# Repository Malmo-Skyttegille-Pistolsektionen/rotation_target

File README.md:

# Rotation Target

Software for running timed shooting programs on a rotating target system, built
by and for Malmö Skyttegille Pistolsektionen.

An ESP32-S3 board turns the targets face-on and edge-on to a shooting program
and plays the spoken range commands over an amplifier. A React web app — served
by the board itself over WiFi — starts and stops programs, follows the run live
over Server-Sent Events, and manages the stored programs and audio.

## ⚠️ SAFETY WARNING — READ BEFORE INSTALLING OR OPERATING

**This device moves steel on a live firing range, and it moves it on a timer.**
A target turns because a program said it was time, not because it can see who
is in front of it. It has no idea anyone is downrange.

- **The range's own safety rules and range commands govern the line. This
  software governs nothing.** A program running is not a range that is hot; a
  program stopped is not a range that is safe.
- **NEVER go downrange because the web app says the run has finished.** Confirm
  a cease-fire the way your range already requires — verbally, with firearms
  cleared and benched.
- **NEVER leave the device powered while people are forward of the firing
  line** unless your club has decided that is safe and knows what the targets
  do at power-up.
- **A target turning can injure somebody standing next to it.** Keep clear of
  the mechanism whenever the device is powered.

The targets rest **shown** at boot, deliberately: a target that turns of its own
accord when a board is powered is the failure this project is most concerned
with. That resting state can be changed to suit a target system wired the other
way round, but only over a USB cable, never from the web app — see
[Settings](https://malmo-skyttegille-pistolsektionen.github.io/rotation_target/settings/).

**Do not rely on this software to protect anyone.** It is a convenience for
running programs, not a safety device, and it has no interlock, no sensor, and
no way to know where people are.

**LIABILITY DISCLAIMER:** This project is provided as-is with absolutely no
warranty of any kind. The author(s) accept no responsibility or liability for
any injury, damage, or loss resulting from building, installing, modifying, or
operating this system. You build and use it entirely at your own risk.

---

## Documentation

Everything an operator needs is on the documentation site:

- **[Operator documentation](https://malmo-skyttegille-pistolsektionen.github.io/rotation_target/)**
  — wiring, connecting, running a program, settings, and what the status LED is
  telling you. This is the one to send a club member.
- **[Program editor](https://malmo-skyttegille-pistolsektionen.github.io/rotation_target/editor/)**
  — write and edit programs in a browser with **no device attached**, then
  download the file or open a pull request against this repository. Also useful
  for reading a shipped program without a board in front of you.
- **[Hardware and wiring](https://malmo-skyttegille-pistolsektionen.github.io/rotation_target/hardware/)**
  — what a target system has to do to work, the DB9 pinout, and the transistor
  that does the switching.

## Installing

Releases ship a pre-built firmware image; you do not need a toolchain to put it
on a board. See
[Connecting](https://malmo-skyttegille-pistolsektionen.github.io/rotation_target/connecting/)
for getting the device onto your network afterwards, and
[Settings](https://malmo-skyttegille-pistolsektionen.github.io/rotation_target/settings/)
for adapting a stock image to your own board — the target pin, its polarity,
the audio and LED pins and the device's name are all configurable on the
device, without rebuilding it.

## Target systems

- **[Eigenbrod TP2](https://eigenbrod-schiessanlagen.de/en/products?tx_produkt_produkte%5Baction%5D=show&tx_produkt_produkte%5BL%5D=2&tx_produkt_produkte%5Bprodukt%5D=319&cHash=942340d5971be0a0ac3d26ff3c257c0b)**
  — what this was built against and what it runs on.

Nothing in the firmware is specific to that system. The board speaks no
proprietary protocol to the targets: it closes and opens **one circuit**, and
the target system's own electronics do the rest. Any system driven the same way
should work.

## Layout

| Directory | Holds |
|---|---|
| [`contracts/`](contracts/README.md) | The canonical API contract: OpenAPI for REST v2, AsyncAPI for SSE v2, the program schema |
| [`firmware/`](firmware/README.md) | The ESP-IDF firmware: target IO, audio, storage, REST + SSE server |
| [`webapp/`](webapp/README.md) | The React front end, embedded in the firmware's application image |
| [`resources/`](resources/README.md) | Shipped programs and audio clips flashed onto the device |
| [`docs/`](docs/) | The [decision log](docs/DECISIONS.md), [how releases are cut](docs/RELEASING.md), and the source of the documentation site |

## Contributing

Building, flashing, running it without a device, and the coding standards are
in [`CONTRIBUTING.md`](CONTRIBUTING.md).

## License

MIT — see the `LICENSE` file in each component directory.

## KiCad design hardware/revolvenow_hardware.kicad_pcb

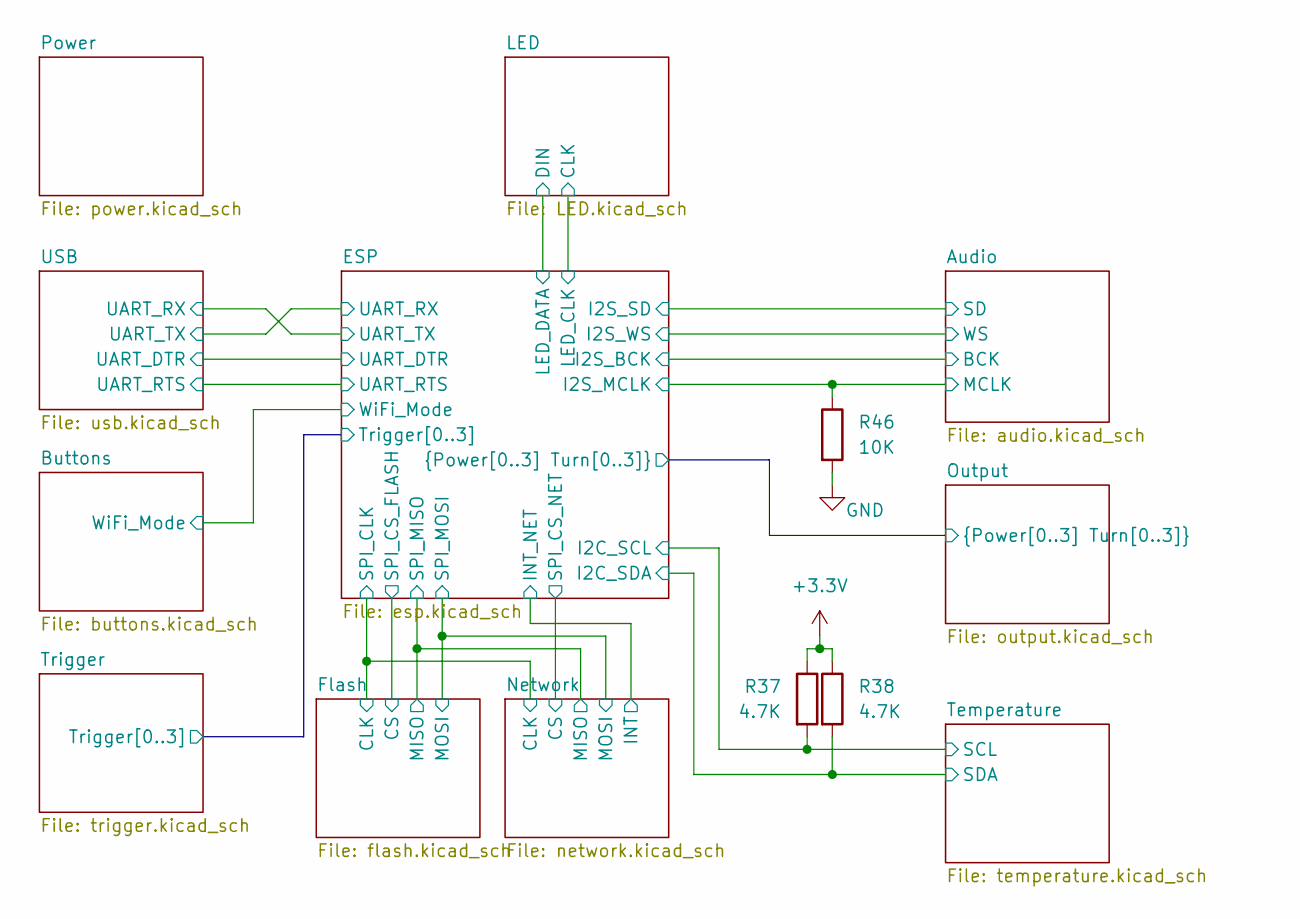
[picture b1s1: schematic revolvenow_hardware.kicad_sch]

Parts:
R37, R38: 4.7K; R_0603_1608Metric_Pad0.98x0.95mm_HandSolder
R46: 10K; R_0603_1608Metric_Pad0.98x0.95mm_HandSolder

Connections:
+3.3V: R37.1, R38.1; also elsewhere on the board
/Audio/MCLK: R46.1; also elsewhere on the board
/ESP/I2C_SCL: R37.2; also elsewhere on the board
/ESP/I2C_SDA: R38.2; also elsewhere on the board
GND: R46.2; also elsewhere on the board

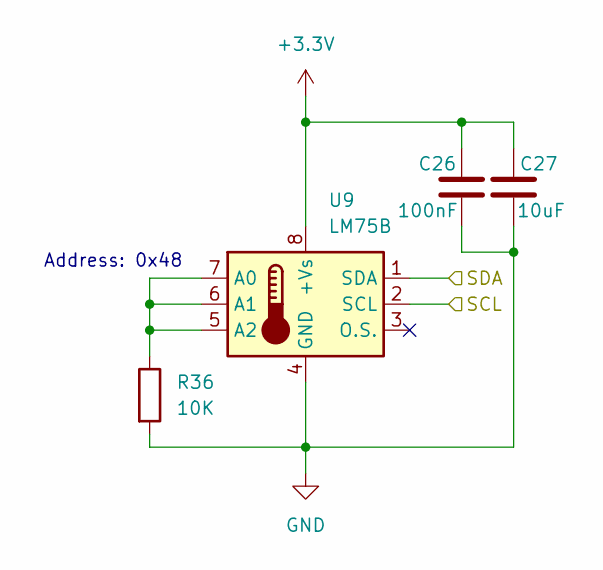
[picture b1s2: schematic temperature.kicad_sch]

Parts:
C26: 100nF; C_0603_1608Metric_Pad1.08x0.95mm_HandSolder
C27: 10uF; C_0603_1608Metric_Pad1.08x0.95mm_HandSolder
R36: 10K; R_0603_1608Metric_Pad0.98x0.95mm_HandSolder
U9: LM75B; SOIC-8_3.9x4.9mm_P1.27mm

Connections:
+3.3V: C26.1, C27.1, U9.8 (+Vs); also elsewhere on the board
/ESP/I2C_SCL: U9.2 (SCL); also elsewhere on the board
/ESP/I2C_SDA: U9.1 (SDA); also elsewhere on the board
GND: C26.2, C27.2, R36.2, U9.4 (GND); also elsewhere on the board
unnamed: R36.1, U9.5 (A2), U9.6 (A1), U9.7 (A0)

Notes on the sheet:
Address: 0x48

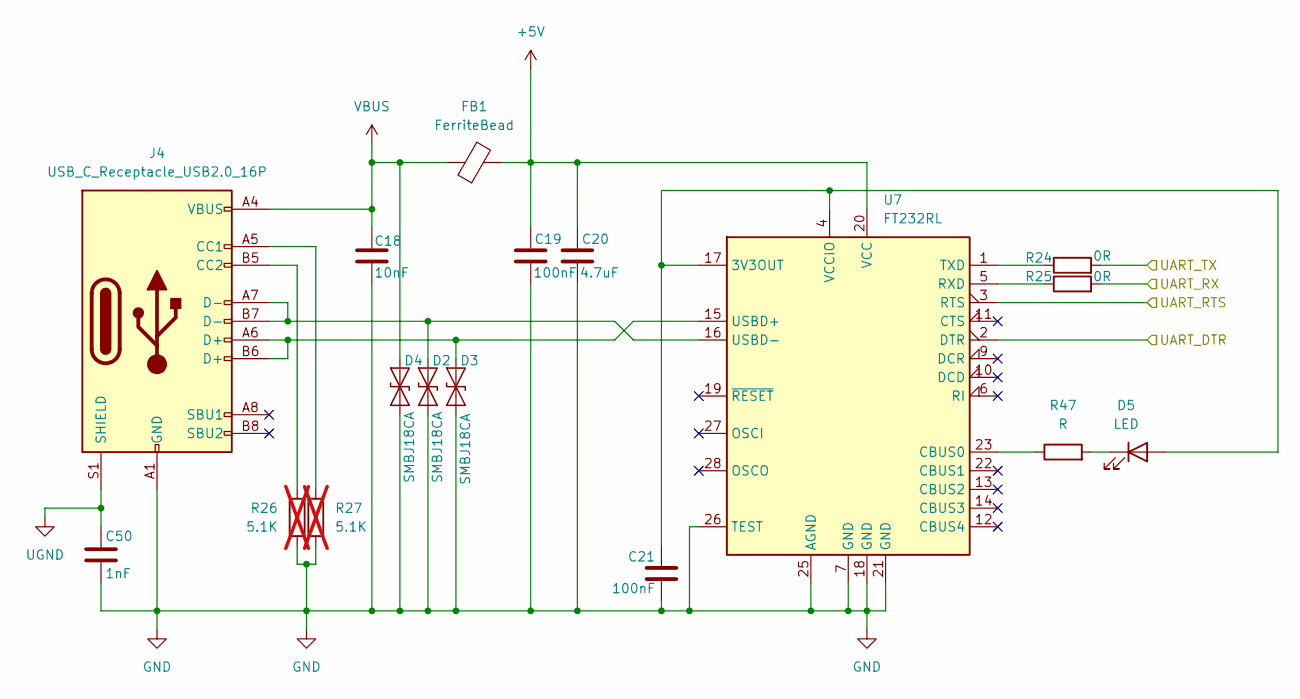
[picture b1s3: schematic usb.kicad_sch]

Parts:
C18: 10nF; C_0603_1608Metric_Pad1.08x0.95mm_HandSolder
C19, C21: 100nF; C_0603_1608Metric_Pad1.08x0.95mm_HandSolder
C20: 4.7uF; C_0603_1608Metric_Pad1.08x0.95mm_HandSolder
C50: 1nF; C_0603_1608Metric_Pad1.08x0.95mm_HandSolder
D2, D3, D4: SMBJ18CA; D_SMB_Handsoldering
D5: LED; LED_0603_1608Metric_Pad1.05x0.95mm_HandSolder
FB1: FerriteBead; R_0805_2012Metric_Pad1.20x1.40mm_HandSolder
J4: USB_C_Receptacle_USB2.0_16P; USB Type-C-02
R24, R25: 0R; R_0603_1608Metric_Pad0.98x0.95mm_HandSolder
R26, R27: 5.1K; R_0603_1608Metric_Pad0.98x0.95mm_HandSolder; not fitted
R47: R; R_0603_1608Metric_Pad0.98x0.95mm_HandSolder
U7: FT232RL; SSOP-28_5.3x10.2mm_P0.65mm

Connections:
+5V: C19.1, C20.1, FB1.2, U7.20 (VCC); also elsewhere on the board
/ESP/UART_DTR: U7.2 (DTR); also elsewhere on the board
/ESP/UART_RTS: U7.3 (RTS); also elsewhere on the board
/ESP/UART_RX: R24.2; also elsewhere on the board
/ESP/UART_TX: R25.2; also elsewhere on the board
GND: C18.2, C19.2, C20.2, C21.2, C50.1, D2.1 (A1), D3.1 (A1), D4.1 (A1), J4.A1 (GND), J4.A12 (GND), J4.B1 (GND), J4.B12 (GND), R26.2, R27.2, U7.7 (GND), U7.18 (GND), U7.21 (GND), U7.25 (AGND), U7.26 (TEST); also elsewhere on the board
unnamed: D2.2 (A2), J4.A7 (D-), J4.B7 (D-), U7.16 (USBD-)
unnamed: D3.2 (A2), J4.A6 (D+), J4.B6 (D+), U7.15 (USBD+)
unnamed: C21.1, D5.2 (A), U7.4 (VCCIO), U7.17 (3V3OUT)
unnamed: D5.1 (K), R47.2
unnamed: J4.A5 (CC1), R27.1
unnamed: J4.B5 (CC2), R26.1
unnamed: R47.1, U7.23 (CBUS0)
unnamed: R25.1, U7.5 (RXD)
unnamed: R24.1, U7.1 (TXD)
UGND: C50.2, J4.S1 (SHIELD)
VBUS: C18.1, D4.2 (A2), FB1.1, J4.A4 (VBUS), J4.A9 (VBUS), J4.B4 (VBUS), J4.B9 (VBUS)

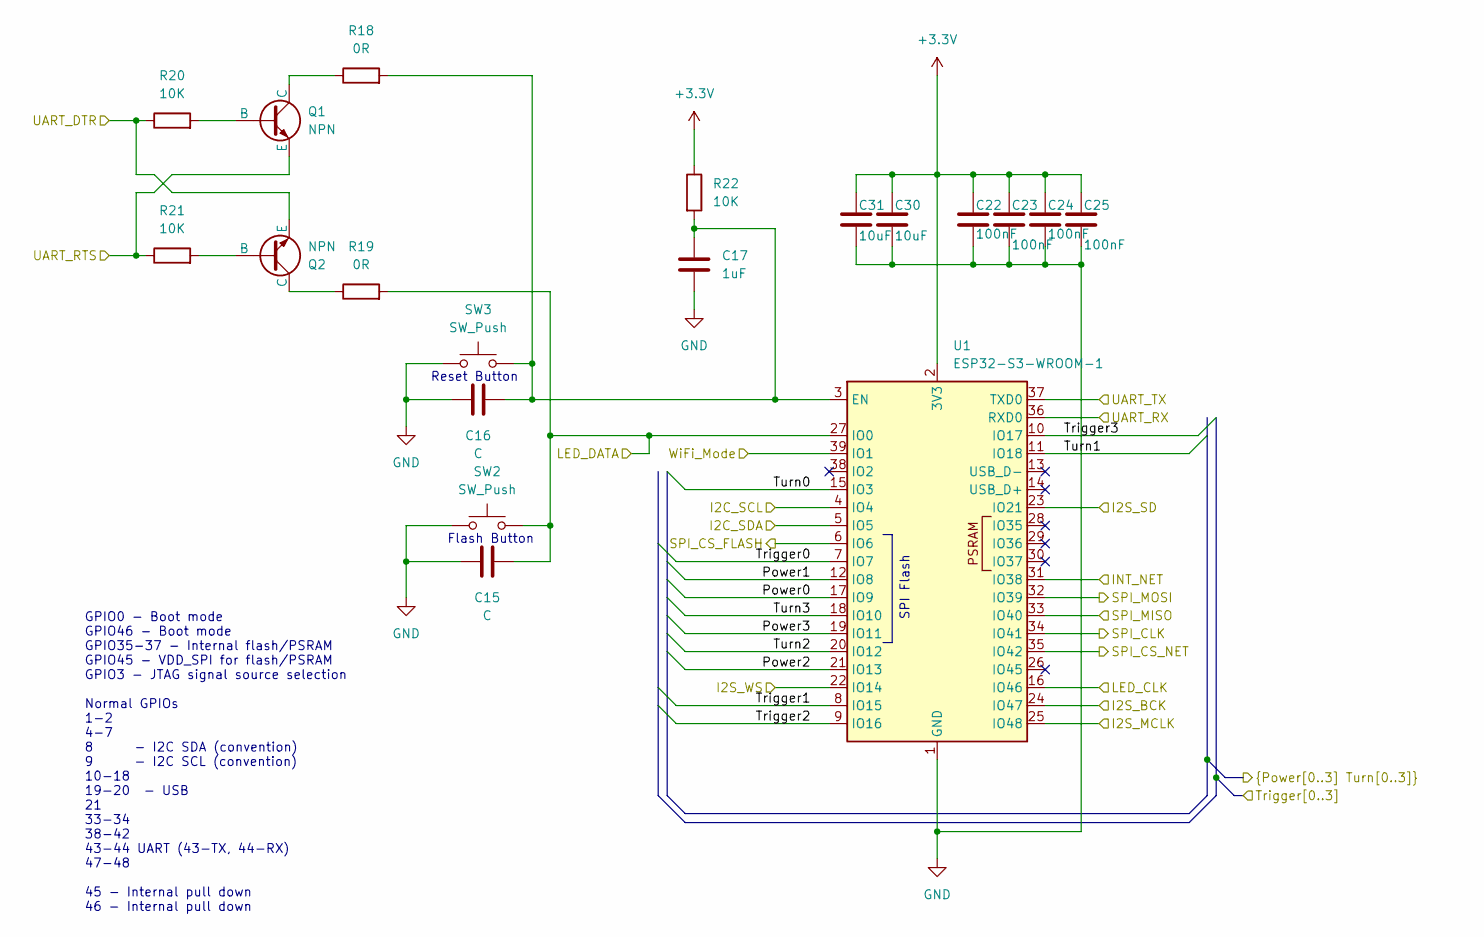
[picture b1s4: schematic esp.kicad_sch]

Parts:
C15, C16: C; C_0603_1608Metric_Pad1.08x0.95mm_HandSolder
C17: 1uF; C_0603_1608Metric_Pad1.08x0.95mm_HandSolder
C22, C23, C24, C25: 100nF; C_0603_1608Metric_Pad1.08x0.95mm_HandSolder
C30, C31: 10uF; C_0603_1608Metric_Pad1.08x0.95mm_HandSolder
Q1, Q2: NPN; SOT-23_Handsoldering
R18, R19: 0R; R_0603_1608Metric_Pad0.98x0.95mm_HandSolder
R20, R21, R22: 10K; R_0603_1608Metric_Pad0.98x0.95mm_HandSolder
SW2, SW3: SW_Push; SW_SPST_PTS645Sx43SMTR92
U1: ESP32-S3-WROOM-1

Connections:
+3.3V: C22.1, C23.1, C24.1, C25.1, C30.1, C31.1, R22.1, U1.2 (3V3); also elsewhere on the board
/Audio/BCK: U1.24 (IO47); also elsewhere on the board
/Audio/MCLK: U1.25 (IO48); also elsewhere on the board
/Audio/SD: U1.23 (IO21); also elsewhere on the board
/Audio/WS: U1.22 (IO14); also elsewhere on the board
/Buttons/WiFi_Mode: U1.39 (IO1); also elsewhere on the board
/ESP/I2C_SCL: U1.4 (IO4); also elsewhere on the board
/ESP/I2C_SDA: U1.5 (IO5); also elsewhere on the board
/ESP/INT_NET: U1.31 (IO38); also elsewhere on the board
/ESP/LED_CLK: U1.16 (IO46); also elsewhere on the board
/ESP/LED_DATA: C15.2, R19.2, SW2.2, U1.27 (IO0); also elsewhere on the board
/ESP/Power0: U1.17 (IO9); also elsewhere on the board
/ESP/Power1: U1.12 (IO8); also elsewhere on the board
/ESP/Power2: U1.21 (IO13); also elsewhere on the board
/ESP/Power3: U1.19 (IO11); also elsewhere on the board
/ESP/SPI_CLK: U1.34 (IO41); also elsewhere on the board
/ESP/SPI_CS_FLASH: U1.6 (IO6); also elsewhere on the board
/ESP/SPI_CS_NET: U1.35 (IO42); also elsewhere on the board
/ESP/SPI_MISO: U1.33 (IO40); also elsewhere on the board
/ESP/SPI_MOSI: U1.32 (IO39); also elsewhere on the board
/ESP/Trigger0: U1.7 (IO7); also elsewhere on the board
/ESP/Trigger1: U1.8 (IO15); also elsewhere on the board
/ESP/Trigger2: U1.9 (IO16); also elsewhere on the board
/ESP/Trigger3: U1.10 (IO17); also elsewhere on the board
/ESP/Turn0: U1.15 (IO3); also elsewhere on the board
/ESP/Turn1: U1.11 (IO18); also elsewhere on the board
/ESP/Turn2: U1.20 (IO12); also elsewhere on the board
/ESP/Turn3: U1.18 (IO10); also elsewhere on the board
/ESP/UART_DTR: Q2.3 (E), R20.1; also elsewhere on the board
/ESP/UART_RTS: Q1.3 (E), R21.1; also elsewhere on the board
/ESP/UART_RX: U1.36 (RXD0); also elsewhere on the board
/ESP/UART_TX: U1.37 (TXD0); also elsewhere on the board
GND: C15.1, C16.1, C17.2, C22.2, C23.2, C24.2, C25.2, C30.2, C31.2, SW2.1, SW3.2, U1.1 (GND), U1.40 (GND), U1.41 (GND); also elsewhere on the board
unnamed: Q1.2 (B), R20.2
unnamed: Q1.1 (C), R18.1
unnamed: Q2.2 (B), R21.2
unnamed: Q2.1 (C), R19.1
unnamed: C16.2, C17.1, R18.2, R22.2, SW3.1, U1.3 (EN)

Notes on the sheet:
SPI Flash
Reset Button
Flash Button
GPIO0 - Boot mode GPIO46 - Boot mode GPIO35-37 - Internal flash/PSRAM GPIO45 - VDD_SPI for flash/PSRAM GPIO3 - JTAG signal source selection Normal GPIOs 1-2 4-7 8 - I2C SDA (convention) 9 - I2C SCL (convention) 10-18 19-20 - USB 21 33-34 38-42 43-44 UART (43-TX, 44-RX) 47-48 45 - Internal pull down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

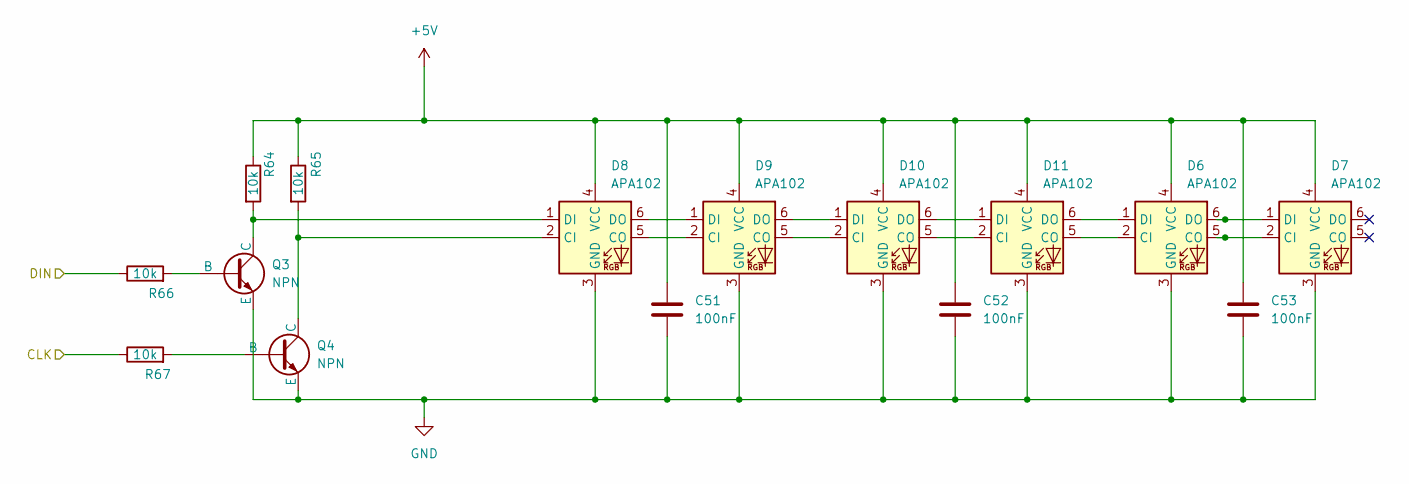
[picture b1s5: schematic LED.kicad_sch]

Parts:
C51, C52, C53: 100nF; C_0603_1608Metric_Pad1.08x0.95mm_HandSolder
D6, D7, D8, D9, D10, D11: APA102; LED_RGB_5050-6
Q3, Q4: NPN; SOT-23_Handsoldering
R64, R65, R66, R67: 10k; R_0603_1608Metric_Pad0.98x0.95mm_HandSolder

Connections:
+5V: C51.1, C52.1, C53.1, D6.4 (VCC), D7.4 (VCC), D8.4 (VCC), D9.4 (VCC), D10.4 (VCC), D11.4 (VCC), R64.1, R65.1; also elsewhere on the board
/ESP/LED_CLK: R67.1; also elsewhere on the board
/ESP/LED_DATA: R66.1; also elsewhere on the board
GND: C51.2, C52.2, C53.2, D6.3 (GND), D7.3 (GND), D8.3 (GND), D9.3 (GND), D10.3 (GND), D11.3 (GND), Q3.3 (E), Q4.3 (E); also elsewhere on the board
unnamed: D6.5 (CO), D7.2 (CI)
unnamed: D6.6 (DO), D7.1 (DI)
unnamed: D8.2 (CI), Q4.1 (C), R65.2
unnamed: D8.5 (CO), D9.2 (CI)
unnamed: D8.1 (DI), Q3.1 (C), R64.2
unnamed: D8.6 (DO), D9.1 (DI)
unnamed: D9.5 (CO), D10.2 (CI)
unnamed: D10.5 (CO), D11.2 (CI)
unnamed: D9.6 (DO), D10.1 (DI)
unnamed: D10.6 (DO), D11.1 (DI)
unnamed: D6.2 (CI), D11.5 (CO)
unnamed: D6.1 (DI), D11.6 (DO)
unnamed: Q3.2 (B), R66.2
unnamed: Q4.2 (B), R67.2

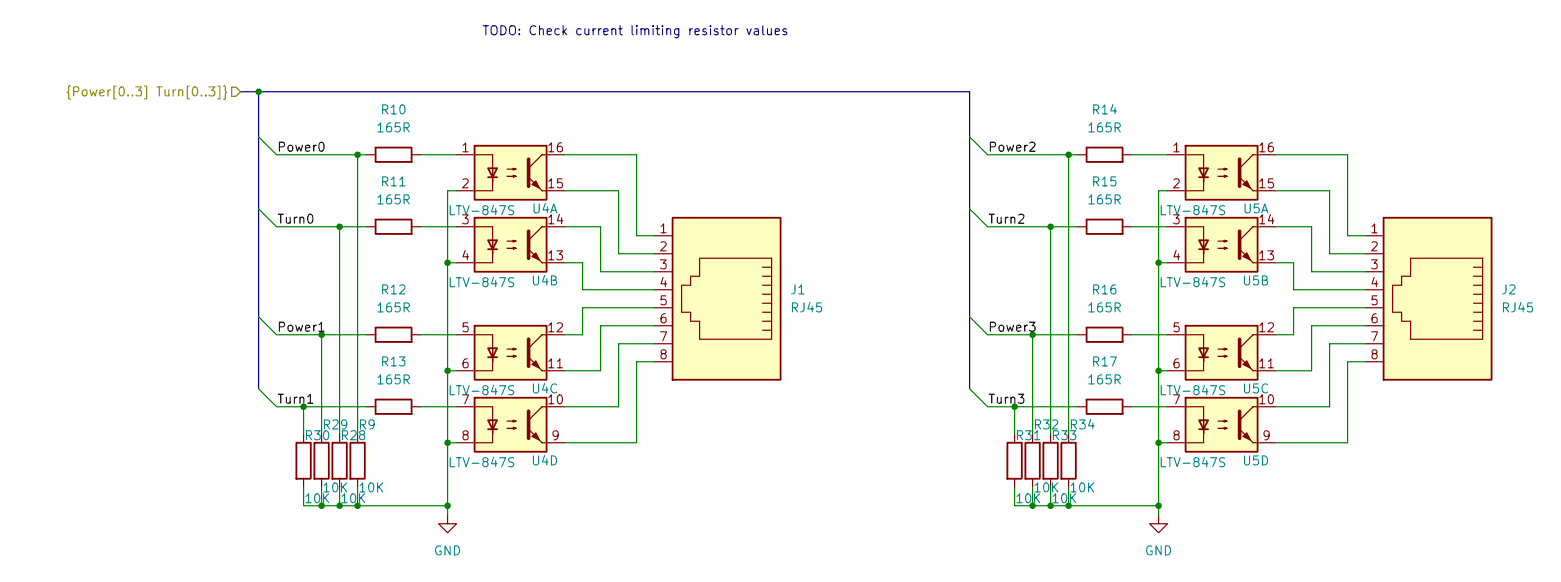
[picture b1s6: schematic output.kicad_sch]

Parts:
J1, J2: RJ45
R9, R28, R29, R30, R31, R32, R33, R34: 10K; R_0603_1608Metric_Pad0.98x0.95mm_HandSolder
R10, R11, R12, R13, R14, R15, R16, R17: 165R; R_0603_1608Metric_Pad0.98x0.95mm_HandSolder
U4, U5: LTV-847S; SMDIP-16_W9.53mm

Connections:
/ESP/Power0: R9.1, R10.1; also elsewhere on the board
/ESP/Power1: R12.1, R29.1; also elsewhere on the board
/ESP/Power2: R14.1, R34.1; also elsewhere on the board
/ESP/Power3: R16.1, R32.1; also elsewhere on the board
/ESP/Turn0: R11.1, R28.1; also elsewhere on the board
/ESP/Turn1: R13.1, R30.1; also elsewhere on the board
/ESP/Turn2: R15.1, R33.1; also elsewhere on the board
/ESP/Turn3: R17.1, R31.1; also elsewhere on the board
GND: R9.2, R28.2, R29.2, R30.2, R31.2, R32.2, R33.2, R34.2, U4.2, U4.4, U4.6, U4.8, U5.2, U5.4, U5.6, U5.8; also elsewhere on the board
unnamed: J1.1, U4.16
unnamed: J1.2, U4.15
unnamed: J1.3, U4.14
unnamed: J1.4, U4.13
unnamed: J1.5, U4.12
unnamed: J1.6, U4.11
unnamed: J1.7, U4.10
unnamed: J1.8, U4.9
unnamed: J2.1, U5.16
unnamed: J2.2, U5.15
unnamed: J2.3, U5.14
unnamed: J2.4, U5.13
unnamed: J2.5, U5.12
unnamed: J2.6, U5.11
unnamed: J2.7, U5.10
unnamed: J2.8, U5.9
unnamed: R10.2, U4.1
unnamed: R11.2, U4.3
unnamed: R12.2, U4.5
unnamed: R13.2, U4.7
unnamed: R14.2, U5.1
unnamed: R15.2, U5.3
unnamed: R16.2, U5.5
unnamed: R17.2, U5.7

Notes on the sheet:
TODO: Check current limiting resistor values

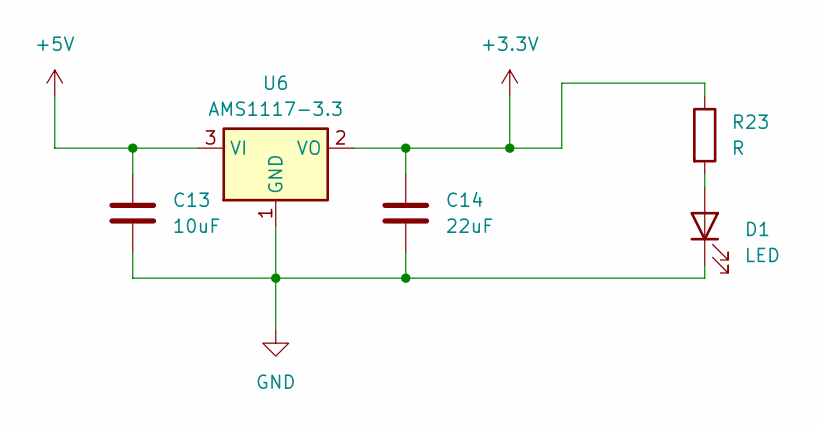
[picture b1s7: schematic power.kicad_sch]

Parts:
C13: 10uF; C_0603_1608Metric_Pad1.08x0.95mm_HandSolder
C14: 22uF; C_0603_1608Metric_Pad1.08x0.95mm_HandSolder
D1: LED; LED_0603_1608Metric_Pad1.05x0.95mm_HandSolder
R23: R; R_0603_1608Metric_Pad0.98x0.95mm_HandSolder
U6: AMS1117-3.3; SOT-223

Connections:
+3.3V: C14.1, R23.1, U6.2 (VO); also elsewhere on the board
+5V: C13.1, U6.3 (VI); also elsewhere on the board
GND: C13.2, C14.2, D1.1 (K), U6.1 (GND); also elsewhere on the board
unnamed: D1.2 (A), R23.2

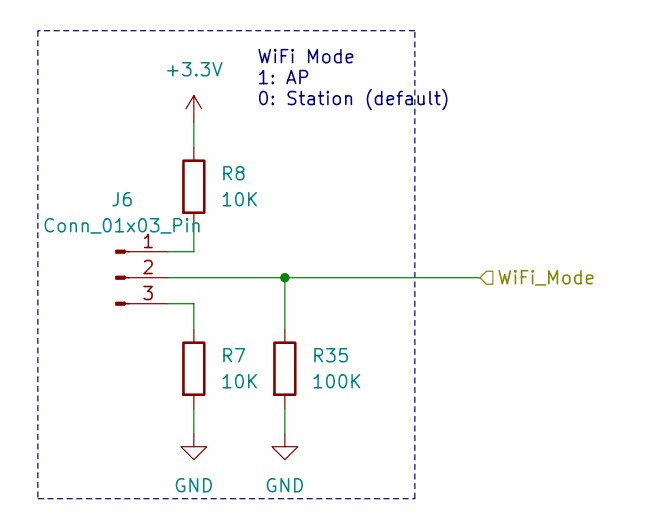
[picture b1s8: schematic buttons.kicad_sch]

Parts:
J6: Conn_01x03_Pin; PinHeader_1x03_P2.54mm_Vertical
R7, R8: 10K; R_0603_1608Metric_Pad0.98x0.95mm_HandSolder
R35: 100K; R_0603_1608Metric_Pad0.98x0.95mm_HandSolder

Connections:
+3.3V: R8.1; also elsewhere on the board
/Buttons/WiFi_Mode: J6.2, R35.1; also elsewhere on the board
GND: R7.2, R35.2; also elsewhere on the board
unnamed: J6.1, R8.2
unnamed: J6.3, R7.1

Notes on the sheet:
WiFi Mode 1: AP 0: Station (default)

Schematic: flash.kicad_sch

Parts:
C28: 100nF; C_0603_1608Metric_Pad1.08x0.95mm_HandSolder
C29: 10uF; C_0603_1608Metric_Pad1.08x0.95mm_HandSolder
R39: 10K; R_0603_1608Metric_Pad0.98x0.95mm_HandSolder
U8: MX25L3233FM; SOIC-16W_7.5x10.3mm_P1.27mm

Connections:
+3.3V: C28.1, C29.1, R39.1, U8.2 (VCC); also elsewhere on the board
/ESP/SPI_CLK: U8.16 (SCLK); also elsewhere on the board
/ESP/SPI_CS_FLASH: U8.7 (~CS); also elsewhere on the board
/ESP/SPI_MISO: U8.8 (SO/SIO1); also elsewhere on the board
/ESP/SPI_MOSI: U8.15 (SI/SIO0); also elsewhere on the board
GND: C28.2, C29.2, U8.10 (GND); also elsewhere on the board
unnamed: R39.2, U8.1 (~HOLD/SIO3), U8.9 (~WP/SIO2)

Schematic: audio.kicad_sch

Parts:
C1, C2: 2.2uF; C_0603_1608Metric_Pad1.08x0.95mm_HandSolder
C3, C4, C5, C6: 0.1uF; C_0603_1608Metric_Pad1.08x0.95mm_HandSolder
C7, C8, C11, C12: 10uF; C_0603_1608Metric_Pad1.08x0.95mm_HandSolder
C9, C10: 2.2nF; C_0603_1608Metric_Pad1.08x0.95mm_HandSolder
J7: AudioJack4; AudioJack PJ-320A
R5, R6: 470R; R_0603_1608Metric_Pad0.98x0.95mm_HandSolder
R44, R45: 10K; R_0603_1608Metric_Pad0.98x0.95mm_HandSolder
U2: PCM5102A; TSSOP-20_4.4x6.5mm_P0.65mm

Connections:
+3.3V: C6.1, C8.1, R45.1, U2.20 (DVDD); also elsewhere on the board
+3.3VA_Audio: C3.1, C4.1, C11.1, C12.1, U2.1 (CPVDD), U2.8 (AVDD)
/Audio/BCK: U2.13 (BCK); also elsewhere on the board
/Audio/MCLK: U2.12 (SCK); also elsewhere on the board
/Audio/SD: U2.14 (DIN); also elsewhere on the board
/Audio/WS: U2.15 (LRCK); also elsewhere on the board
GND: R44.2; also elsewhere on the board
GNDA: C2.2, C3.2, C4.2, C9.2, C10.2, C11.2, C12.2, J7.R2, J7.S, U2.3 (CPGND), U2.9 (AGND)
unnamed: C9.1, J7.T, R5.2
unnamed: C10.1, J7.R1, R6.2
unnamed: C1.2, U2.4 (CAPM)
unnamed: C1.1, U2.2 (CAPP)
unnamed: R44.1, U2.10 (DEMP), U2.11 (FLT), U2.16 (FMT)
unnamed: C5.1, C6.2, C7.1, C8.2, U2.19 (DGND)
unnamed: C5.2, C7.2, U2.18 (LDOO)
unnamed: R5.1, U2.6 (OUTL)
unnamed: R6.1, U2.7 (OUTR)
unnamed: C2.1, U2.5 (VNEG)
unnamed: R45.2, U2.17 (XSMT)

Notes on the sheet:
TODO: Verify Mode and I2S input

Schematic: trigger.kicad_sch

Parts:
J3: RJ45
R1, R2, R3, R4: 10K; R_0603_1608Metric_Pad0.98x0.95mm_HandSolder
R40: 165R; R_0603_1608Metric_Pad0.98x0.95mm_HandSolder
R41: 250R; R_0603_1608Metric_Pad0.98x0.95mm_HandSolder
R42: 600R; R_0603_1608Metric_Pad0.98x0.95mm_HandSolder
R43: R; R_0603_1608Metric_Pad0.98x0.95mm_HandSolder
U3: LTV-847S; SMDIP-16_W9.53mm

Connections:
+3.3V: R1.1, R2.1, R3.1, R4.1; also elsewhere on the board
/ESP/Trigger0: R1.2, U3.16; also elsewhere on the board
/ESP/Trigger1: R2.2, U3.14; also elsewhere on the board
/ESP/Trigger2: R3.2, U3.12; also elsewhere on the board
/ESP/Trigger3: R4.2, U3.10; also elsewhere on the board
GND: U3.9, U3.11, U3.13, U3.15; also elsewhere on the board
unnamed: J3.1, U3.8
unnamed: J3.2, R43.1
unnamed: J3.3, U3.6
unnamed: J3.4, R42.1
unnamed: J3.5, U3.4
unnamed: J3.6, R41.1
unnamed: J3.7, U3.2
unnamed: J3.8, R40.1
unnamed: R40.2, U3.1
unnamed: R41.2, U3.3
unnamed: R42.2, U3.5
unnamed: R43.2, U3.7

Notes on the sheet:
7-8: 3.3V 5-6: 5.0V 3-4: 12.0V 1-2: ?V

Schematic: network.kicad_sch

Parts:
C34, C38, C39, C40, C41, C42, C43: 100nF; C_0603_1608Metric_Pad1.08x0.95mm_HandSolder
C35, C44: 10uF; C_0603_1608Metric_Pad1.08x0.95mm_HandSolder
C36, C46: 10nF; C_0603_1608Metric_Pad1.08x0.95mm_HandSolder
C37: 4.7uF; C_0603_1608Metric_Pad1.08x0.95mm_HandSolder
C45: 22nF; C_0603_1608Metric_Pad1.08x0.95mm_HandSolder
C47, C48: 6.8nF; C_0603_1608Metric_Pad1.08x0.95mm_HandSolder
C49: 1nF/2kV; C_1206_3216Metric_Pad1.33x1.80mm_HandSolder
L1: L; L_0603_1608Metric_Pad1.05x0.95mm_HandSolder
R48, R49: 10k; R_0603_1608Metric_Pad0.98x0.95mm_HandSolder
R50: 12.4K; R_0603_1608Metric_Pad0.98x0.95mm_HandSolder
R53, R54, R55, R56: 33R; R_0603_1608Metric_Pad0.98x0.95mm_HandSolder
R57, R58, R60, R61: 49R9; R_0603_1608Metric_Pad0.98x0.95mm_HandSolder
R59: 10R; R_0603_1608Metric_Pad0.98x0.95mm_HandSolder
R62, R63: 330R; R_0603_1608Metric_Pad0.98x0.95mm_HandSolder
U10: W5500; LQFP-48_7x7mm_P0.5mm
U11: J0026D21BNL; RJ45_PulseJack_MechB
Y2: 25MHz; Oscillator_SMD_Abracon_ASE-4Pin_3.2x2.5mm

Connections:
+3.3V: C34.1, C35.1, L1.1, R48.1, R49.1, U10.28 (VDD), Y2.4 (Vdd); also elsewhere on the board
+3.3VA_Ethernet: C38.1, C39.1, C40.1, C41.1, C42.1, C43.1, C44.1, L1.2, R57.1, R58.1, R59.1, U10.4 (AVDD), U10.8 (AVDD), U10.11 (AVDD), U10.15 (AVDD), U10.17 (AVDD), U10.21 (AVDD)
/ESP/INT_NET: U10.36 (~INT); also elsewhere on the board
/ESP/SPI_CLK: U10.33 (SCLK); also elsewhere on the board
/ESP/SPI_CS_NET: U10.32 (~SCS); also elsewhere on the board
/ESP/SPI_MISO: U10.34 (MISO); also elsewhere on the board
/ESP/SPI_MOSI: U10.35 (MOSI); also elsewhere on the board
CGND: C49.2, U11.4 (CHS_GND), U11.5 (CHS_GND), U11.SH
GND: C34.2, C35.2, C36.2, C37.2, C38.2, C39.2, C40.2, C41.2, C42.2, C43.2, C44.2, C45.2, C46.2, C49.1, R50.2, U10.3 (AGND), U10.9 (AGND), U10.14 (AGND), U10.16 (AGND), U10.19 (AGND), U10.29 (GND), U10.48 (AGND), U11.10, U11.11, Y2.2 (GND); also elsewhere on the board
unnamed: C47.1, R56.2, R60.1
unnamed: C48.1, R55.2, R61.1
unnamed: R62.1, U11.9
unnamed: R63.1, U11.12
unnamed: C36.1, U10.22 (1V2O)
unnamed: R63.2, U10.27 (ACTLED)
unnamed: R50.1, U10.10 (EXRES1)
unnamed: R62.2, U10.25 (LINKLED)
unnamed: R49.2, U10.43 (PMODE2), U10.44 (PMODE1), U10.45 (PMODE0)
unnamed: R55.1, U10.5 (RXN)
unnamed: R56.1, U10.6 (RXP)
unnamed: C37.1, U10.20 (TOCAP)
unnamed: R53.1, U10.1 (TXN)
unnamed: R54.1, U10.2 (TXP)
unnamed: U10.30 (XI/CLKIN), Y2.3 (OUT)
unnamed: C46.1, R60.2, R61.2, U11.6 (RCT)
unnamed: C47.2, U11.7 (RD+)
unnamed: C48.2, U11.8 (RD-)
unnamed: C45.1, R59.2, U11.3 (TCT)
unnamed: R54.2, R58.2, U11.1 (TD+)
unnamed: R53.2, R57.2, U11.2 (TD-)
unnamed: R48.2, Y2.1 (EN)

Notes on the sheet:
PMODE = 111 10/100Mbps auto-negotiation

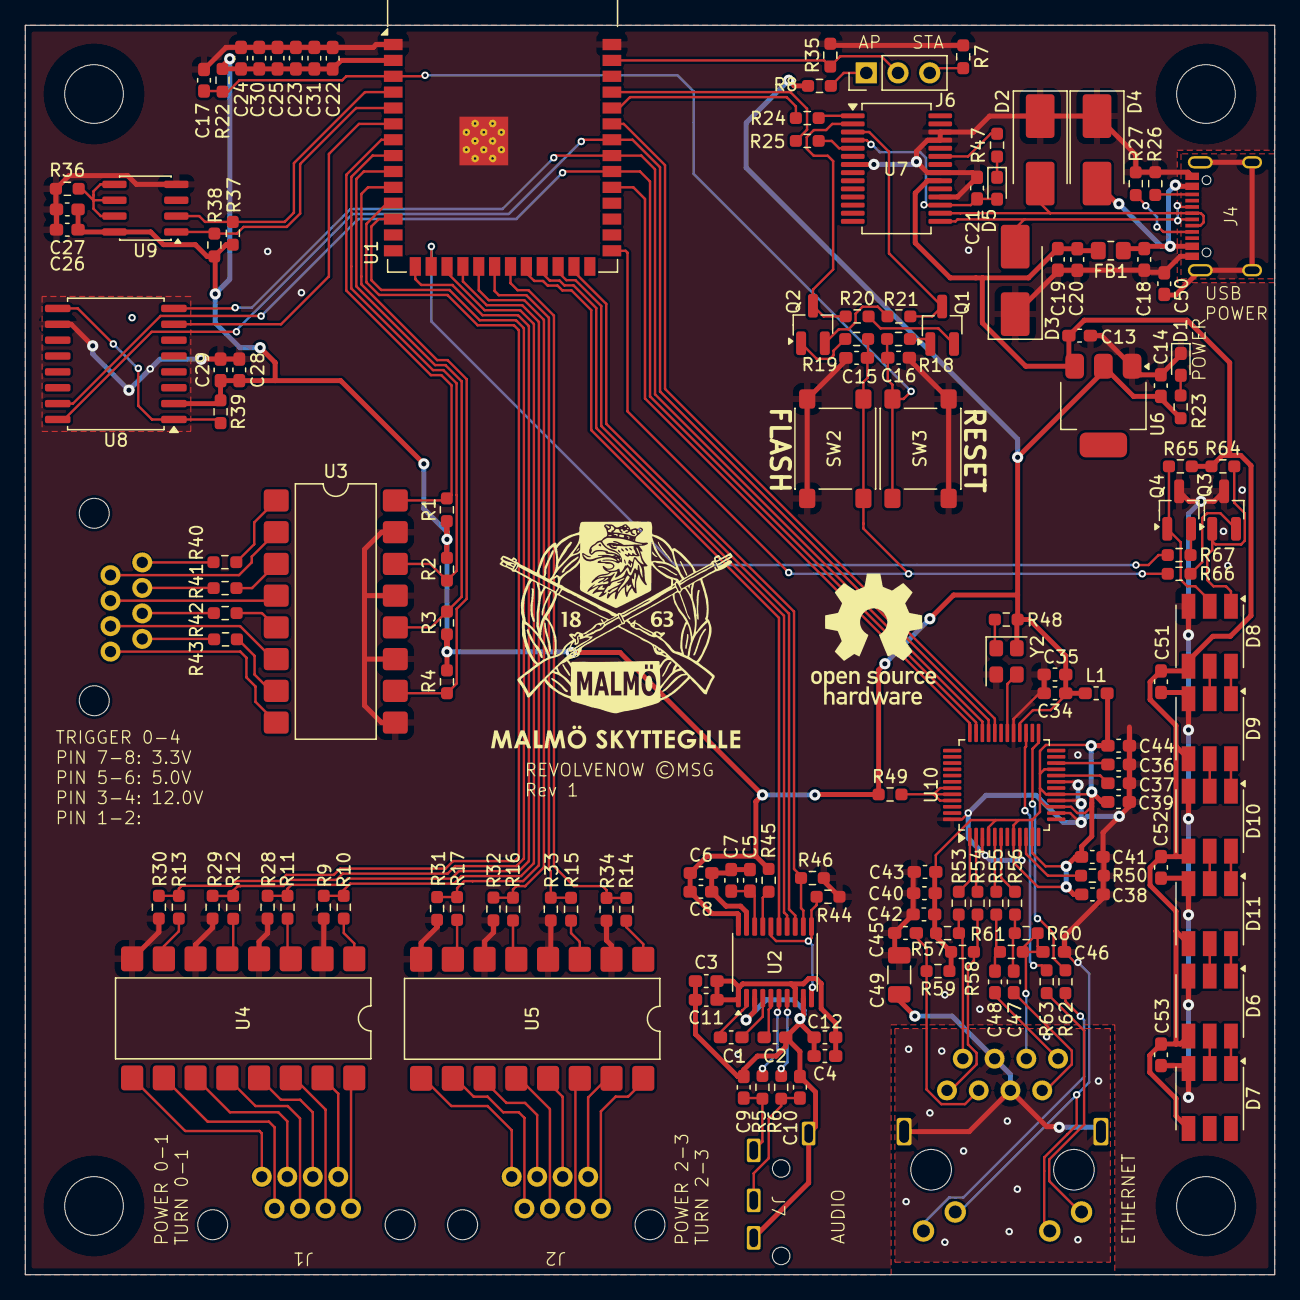
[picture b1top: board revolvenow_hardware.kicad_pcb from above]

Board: 2 copper layers, 100.0 x 100.0 mm, 153 parts (0 on the bottom side), 142 nets.

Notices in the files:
hardware/revolvenow_hardware.kicad_pcb:
REVOLVENOW ©MSG
